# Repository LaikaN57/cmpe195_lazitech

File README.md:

# cmpe195_laztech
**Spring 2016 / Fall 2016**

LazTech is an upgrade kit for the K40 laser cutter/engraver. Both a new hardware motherboard and software printer drivers are included in this project.
## 1 Hardware
## 2 USB Device Side Code
### 2.1 Documentation
There is a lot of good documentaiton in the first link. Some of the documents are subsets of other documents.
* [MPLAB Harmony Integrated Software Framework Documentation](http://www.microchip.com/mplab/mplab-harmony) Note: Click the documentation tab.
  * [MPLAB Harmony Help Document](http://ww1.microchip.com/downloads/en/DeviceDoc/MPLAB%20Harmony%20Help%20%28v1.07.01%29.pdf)
    * [Creating Your Own USB Device Section](http://ww1.microchip.com/downloads/en/DeviceDoc/Volume%20IV%20-%20MPLAB%20Harmony%20Framework%20Reference%20(v1.07.01).pdf#14133)
* [USB Device Class Specifications](http://www.usb.org/developers/docs/devclass_docs/)
  * [USB Device Class Definition for Printing Devices](http://www.usb.org/developers/docs/devclass_docs/usbprint11a021811.pdf)

## 3 USB Host Side Driver
### 3.1 Kernel Source
This is the kernel we will be building our module against.
* [Linux kernel stable tree](https://git.kernel.org/cgit/linux/kernel/git/stable/linux-stable.git/tree/)
* [Linux cross reference](http://lxr.free-electrons.com/) Note: This should take you to the lastest linux-stable version but if not, check what version the master branch is at on the git repo and use that on LXR.

### 3.2 Documentation
Here is some authoritative information on kernel module and usb host development.
* [Documentation](https://git.kernel.org/cgit/linux/kernel/git/stable/linux-stable.git/tree/Documentation)
  * [Building External Modules](https://git.kernel.org/cgit/linux/kernel/git/stable/linux-stable.git/tree/Documentation/kbuild/modules.txt)
  * [usb](https://git.kernel.org/cgit/linux/kernel/git/stable/linux-stable.git/tree/Documentation/usb)

### 3.3 Headers / Sources
These are some of the core includes we will need to get our module and filesystem installed.
* [Include](https://git.kernel.org/cgit/linux/kernel/git/stable/linux-stable.git/tree/include)
  * [linux/module.h](https://git.kernel.org/cgit/linux/kernel/git/stable/linux-stable.git/tree/include/linux/module.h)
  * [linux/usb.h](https://git.kernel.org/cgit/linux/kernel/git/stable/linux-stable.git/tree/include/linux/usb.h)
  * [linux/usb](https://git.kernel.org/cgit/linux/kernel/git/stable/linux-stable.git/tree/include/linux/usb)
* [drivers/usb](https://git.kernel.org/cgit/linux/kernel/git/stable/linux-stable.git/tree/drivers/usb) Note: There is a lot of information in this directory. Check the README.
  * [README](https://git.kernel.org/cgit/linux/kernel/git/stable/linux-stable.git/tree/drivers/usb/README)
  * [class/usblp.c](https://git.kernel.org/cgit/linux/kernel/git/stable/linux-stable.git/tree/drivers/usb/class/usblp.c)

### 3.4 Example USB Drivers
These are some links to different usb drivers that can be used for reference.
* [drivers/usb](https://git.kernel.org/cgit/linux/kernel/git/stable/linux-stable.git/tree/drivers/usb)
  * FTDI USB Single Port Serial Converter (This is what is on almost all of our dev boards.)
    * [serial/ftdi_sio.h](https://git.kernel.org/cgit/linux/kernel/git/stable/linux-stable.git/tree/drivers/usb/serial/ftdi_sio.h)
    * [serial/ftdi_sio.c](https://git.kernel.org/cgit/linux/kernel/git/stable/linux-stable.git/tree/drivers/usb/serial/ftdi_sio.c)

### 3.5 Debugging
* strace (user space tracing)
  * [Ubuntu manuals - strace(1)](http://manpages.ubuntu.com/manpages/wily/en/man1/strace.1.html)
* ftrace (kernel space tracing)
  * [LWN.net - Debugging the kernel using Ftrace - part 1](https://lwn.net/Articles/365835/)
  * [LWN.net - Debugging the kernel using Ftrace - part 2](https://lwn.net/Articles/366796/)
  * `echo ":mod:<your_mod_name>" > set_ftrace_filter` is really useful.

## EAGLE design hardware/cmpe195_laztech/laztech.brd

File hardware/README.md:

# cmpe195_laztech/hardware

This Eagle projects directory. You can add this folder to your Eagle installation to integrate all of the Laztech projects with your workflow.

## 1 Installation
1. Start Eagle
2. Click *Options* > *Directories...*
3. Click in the textbox labeled *Projects*
4. Move the cursor to the end of the line
5. Click *Browse...*
6. Navigate to the cmpe195_laztech git repository
7. Highlight *hardware*
8. Click *Choose*
9. Click *OK*
You should now be able to see the Laztech project(s) under *Projects/hardware* in the Eagle *Control Panel*.

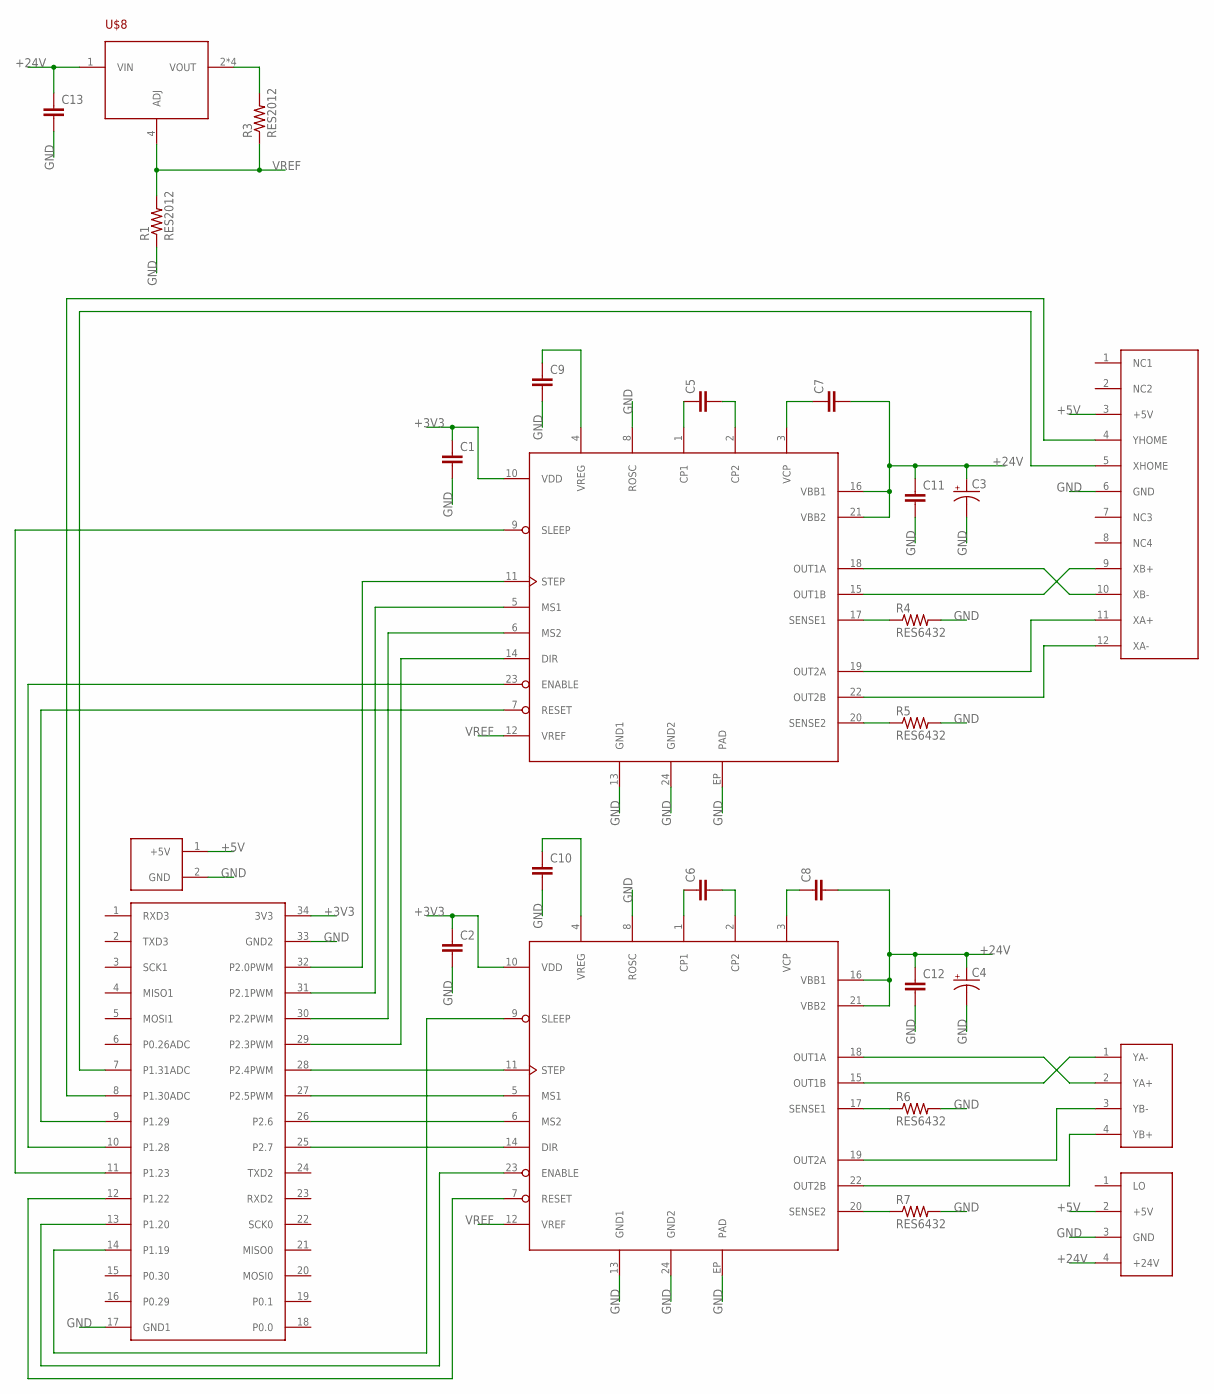
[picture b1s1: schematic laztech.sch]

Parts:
C1, C2, C5, C6, C7, C8, C9, C10, C11, C12, C13: CAP; C2012
C3, C4: PCAP; C6358R
R1, R3: RES2012; R2012
R4, R5, R6, R7: RES6432; R6432
U$1, U$2: A4985SLPTR-T; ETSSOP-24
U$3: SJSUONEX; 2X17
U$4: K40-PWR; MOLEX-KK396-4-RA
U$5: K40-X; MOLEX-FFC-12-RA
U$6: K40-Y; JST-XH-4_RA
U$7: SJSUONEVIN; 1X02
U$8: LM317; SOIC-8

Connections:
+3V3: C1.1, C2.1, U$1.10 (VDD), U$2.10 (VDD), U$3.34 (3V3)
+5V: U$4.2 (+5V), U$5.3 (+5V), U$7.1 (+5V)
+24V: C3.2 (+), C4.2 (+), C7.2, C8.2, C11.1, C12.1, C13.1, U$1.16 (VBB1), U$1.21 (VBB2), U$2.16 (VBB1), U$2.21 (VBB2), U$4.4 (+24V), U$8.1 (VIN)
GND: C1.2, C2.2, C3.1 (-), C4.1 (-), C9.2, C10.2, C11.2, C12.2, C13.2, R1.1, R4.2, R5.2, R6.2, R7.2, U$1.8 (ROSC), U$1.13 (GND1), U$1.24 (GND2), U$1.EP (PAD), U$2.8 (ROSC), U$2.13 (GND1), U$2.24 (GND2), U$2.EP (PAD), U$3.17 (GND1), U$3.33 (GND2), U$4.3 (GND), U$5.6 (GND), U$7.2 (GND)
unnamed: U$1.18 (OUT1A), U$5.10 (XB-)
unnamed: U$1.15 (OUT1B), U$5.9 (XB+)
unnamed: U$1.19 (OUT2A), U$5.11 (XA+)
unnamed: U$1.22 (OUT2B), U$5.12 (XA-)
unnamed: U$2.15 (OUT1B), U$6.1 (YA-)
unnamed: U$2.18 (OUT1A), U$6.2 (YA+)
unnamed: U$2.19 (OUT2A), U$6.3 (YB-)
unnamed: U$2.22 (OUT2B), U$6.4 (YB+)
unnamed: R4.1, U$1.17 (SENSE1)
unnamed: U$3.7 (P1.31ADC), U$5.5 (XHOME)
unnamed: U$3.8 (P1.30ADC), U$5.4 (YHOME)
unnamed: U$2.14 (DIR), U$3.25 (P2.7)
unnamed: U$2.6 (MS2), U$3.26 (P2.6)
unnamed: U$2.5 (MS1), U$3.27 (P2.5PWM)
unnamed: U$2.11 (STEP), U$3.28 (P2.4PWM)
unnamed: U$1.11 (STEP), U$3.32 (P2.0PWM)
unnamed: U$1.5 (MS1), U$3.31 (P2.1PWM)
unnamed: U$1.6 (MS2), U$3.30 (P2.2PWM)
unnamed: U$1.14 (DIR), U$3.29 (P2.3PWM)
unnamed: U$2.23 (ENABLE), U$3.13 (P1.20)
unnamed: U$2.7 (RESET), U$3.12 (P1.22)
unnamed: U$2.9 (SLEEP), U$3.14 (P1.19)
unnamed: U$1.7 (RESET), U$3.9 (P1.29)
unnamed: U$1.23 (ENABLE), U$3.10 (P1.28)
unnamed: U$1.9 (SLEEP), U$3.11 (P1.23)
unnamed: C10.1, U$2.4 (VREG)
unnamed: C6.1, U$2.1 (CP1)
unnamed: C6.2, U$2.2 (CP2)
unnamed: C8.1, U$2.3 (VCP)
unnamed: C9.1, U$1.4 (VREG)
unnamed: C5.1, U$1.1 (CP1)
unnamed: C5.2, U$1.2 (CP2)
unnamed: C7.1, U$1.3 (VCP)
unnamed: R3.2, U$8.2 (VOUT), U$8.3 (VOUT), U$8.6 (VOUT), U$8.7 (VOUT)
unnamed: R5.1, U$1.20 (SENSE2)
unnamed: R6.1, U$2.17 (SENSE1)
unnamed: R7.1, U$2.20 (SENSE2)
VREF: R1.2, R3.1, U$1.12 (VREF), U$2.12 (VREF), U$8.4 (ADJ)

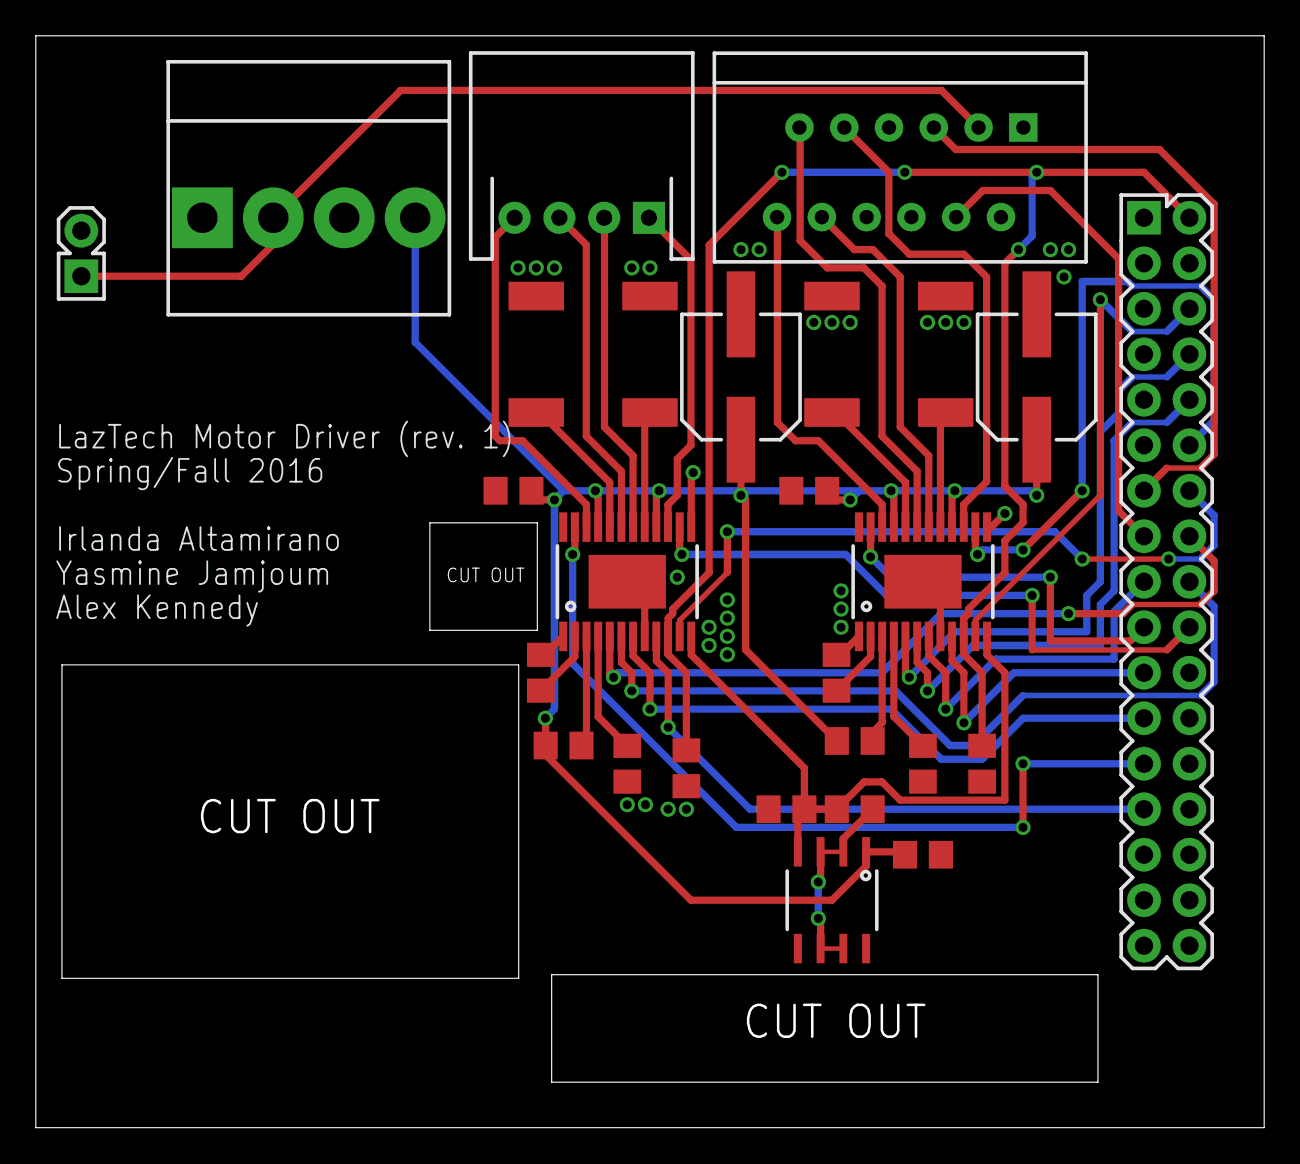
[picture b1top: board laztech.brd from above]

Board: 2 copper layers, 68.6 x 61.0 mm, 27 parts (0 on the bottom side), 42 nets.

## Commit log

2016-03-19 Update README.md
    Added USB Host Side Driver sections.
2016-03-21 Create Eagle project.
    The parts library, schematic, and board have all been initialized. In addition the eagle.epf has been excluded from git because it is a system dependant file.
2016-03-21 Create README.md
    Added installation instructions to the import the Eagle projects.
2016-03-21 Created a linux module skeleton.
    This skeleton can be used for creating a USB driver module or other kernel code as required.
2016-03-21 Create README.md
    Added description of folder.
2016-03-23 Update README.md
    Added Microchip Harmony documentation.
2016-03-23 Update README.md
    Added USB device class specs.
2016-03-23 Update README.md
    Added usblp driver.
2016-04-15 Create test_pdf_gfx_scanner.l
    This file will eventually be compiled and used in MPLabX for use on the device side.
2016-04-16 Create CODE_CutLine_CutCurve
2016-04-16 Update CODE_CutLine_CutCurve
2016-05-01 Added a documentation directory and moved the user README.txt.
2016-05-01 Removed old user README.
2016-05-02 Added some parts to library and started schematic for v1.
2016-05-02 Added initial direct connections with no passives.
2016-05-02 Started board layout and added Rosc to ground.
2016-05-05 Replaced some connectors with SFE connecters.
2016-05-05 Fixed more parts in library.
2016-05-05 Last commit before adding capacitors and other A4985 support hardware.
2016-05-05 Fixed git commit and added eagle temp files to list.
2016-05-05 Added capacitors to sch and brd.
2016-05-06 Added LM317.
2016-05-07 Added pin directions and resistor symbols.
2016-05-07 Fixed directions and swaplevels of all devices.
2016-05-09 Added resistor packages.
2016-05-09 Removed default resistor package varient.
2016-05-09 Pre-route checkpoint.
2016-05-09 Routed stepper motor outputs.
2016-05-09 Partial layout. Still need to route signals to uCPU.
2016-05-09 Vref routed.
2016-05-09 Finished first round of routing.
2016-05-09 Last commit for tonight's work.
2016-05-09 Messed up and made the sch and brd not consistant. Trying to roll back.
2016-05-10 Got brd and sch back on track.
2016-05-10 Almost done with DRC fixes.
2016-05-10 Finished board rev 1.
2016-05-17 Added Alex's dev branch and reconfigured some directories.
2016-09-01 Update and rename CODE_CutLine_CutCurve to Definitions
2016-10-06 Add files via upload
    reading stream character lines between stream and endstream
2016-10-14 Checkpoint upload. About to bork this branch.
2016-10-18 Added firmware directory.
    This includes half of the working input along with a base scanner.
2016-10-18 Added firmware directory.
    This will be used on the LPC but for now and for testing it
    compiles on x86. This version includes half of the input stage and
    a base scanner to be extended to a full output module.
2016-10-20 Added output module to firmware.
2016-10-20 Uploaded miniz and ouput module.
2016-12-21 Added final code products and other code.
2016-12-21 Removed freeRTOS git code.
2016-12-21 Reuploaded freeRTOS code.
